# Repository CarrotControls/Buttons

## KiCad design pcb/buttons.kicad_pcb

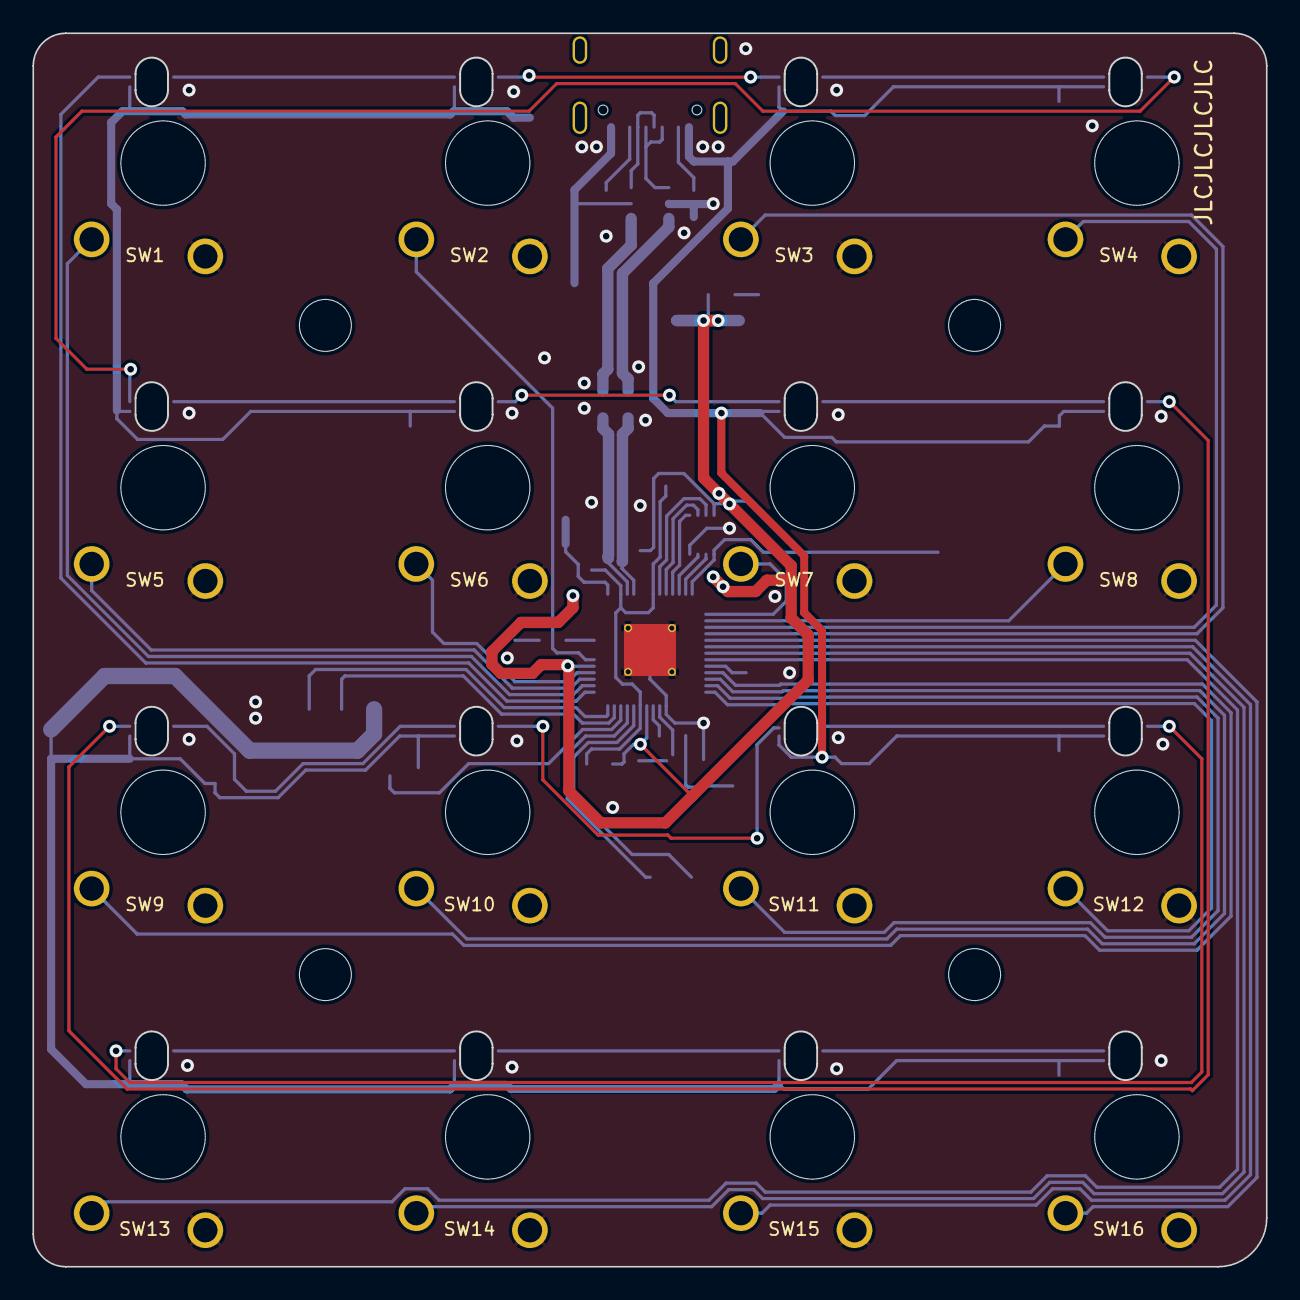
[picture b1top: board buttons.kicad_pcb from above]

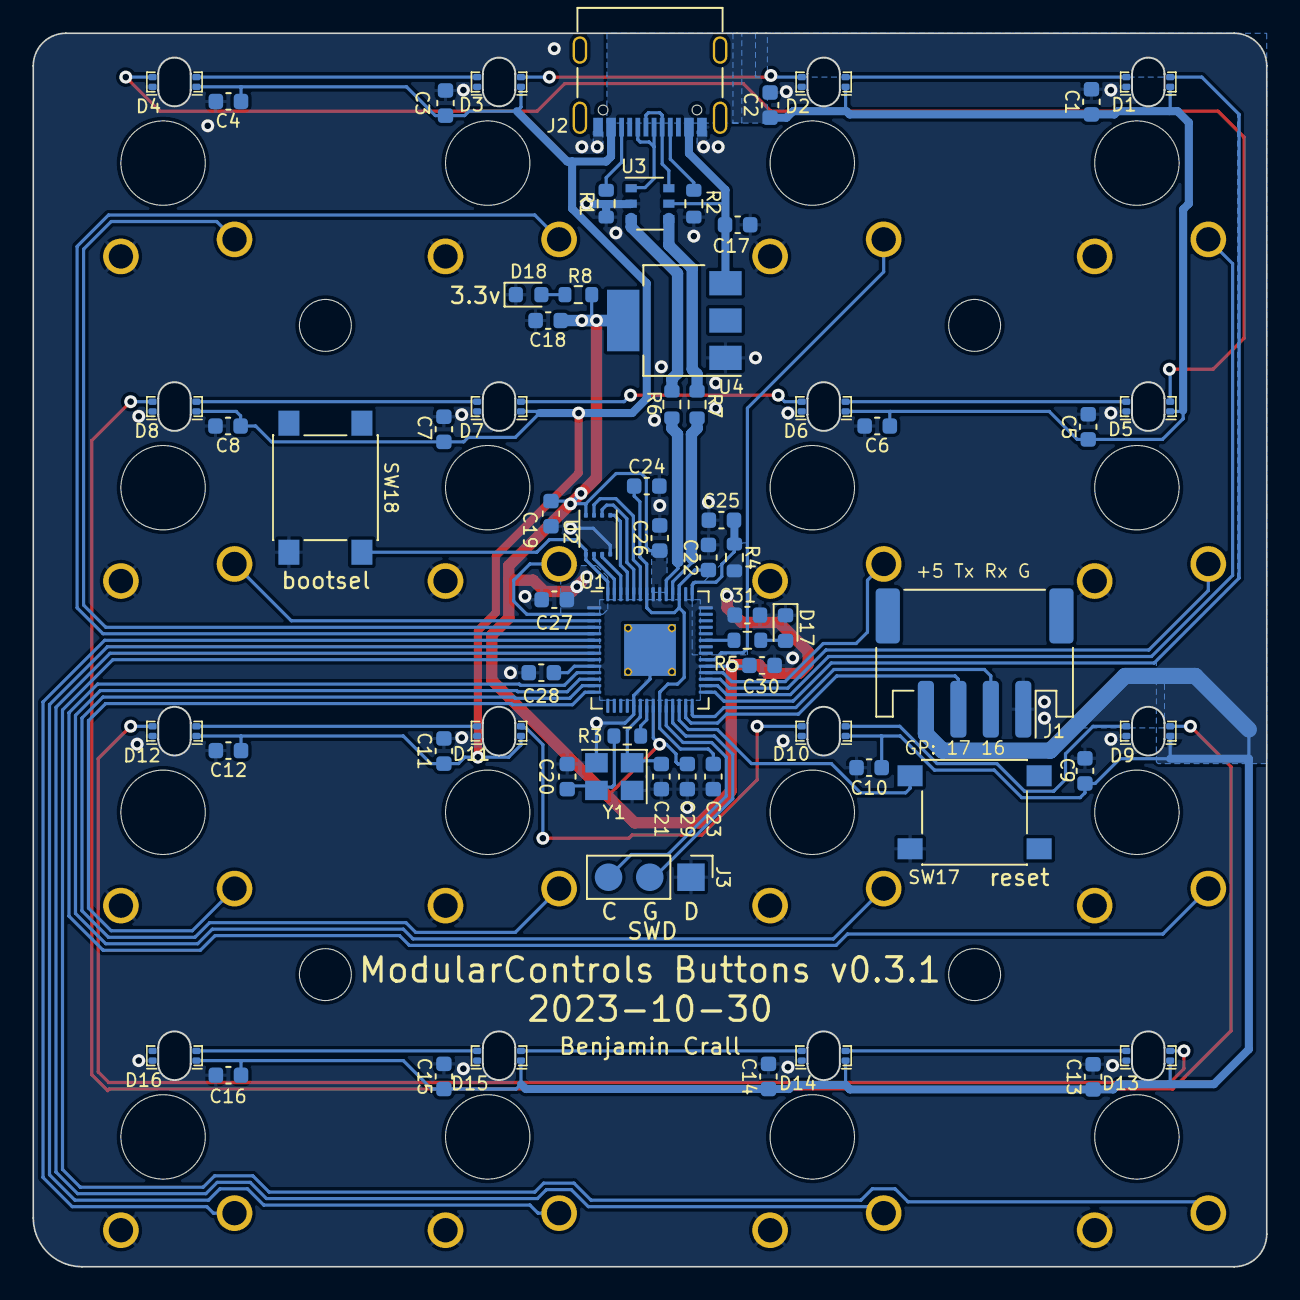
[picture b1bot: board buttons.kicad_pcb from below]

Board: 2 copper layers, 76.0 x 76.0 mm, 87 parts (67 on the bottom side), 62 nets.

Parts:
C1, C2, C3, C4, C5, C6, C7, C8, C9, C10, C11, C12, C13, C14, C15, C16, C17, C19: 10u; C_0603_1608Metric
C18: 22u; C_0603_1608Metric
C20, C21: C_XTL; C_0603_1608Metric
C22, C25: 2.2u; C_0603_1608Metric
C23, C24, C26, C27, C28, C29, C30, C31: 100n; C_0603_1608Metric
D1, D2, D3, D4, D5, D6, D7, D8, D9, D10, D11, D12, D13, D14, D15, D16: WS2812B; Neopixel - Slim Flat - Down
D17, D18: LED_GREEN; LED_0603_1608Metric
H1, H2, H3, H4: MountingHole; MountingHole_3.2mm_M3
J1: Conn_01x04; JST_PH_S4B-PH-SM4-TB_1x04-1MP_P2.00mm_Horizontal
J2: USB_C_Receptacle_USB2.0; USB_C_Receptacle_Palconn_UTC16-G
J3: Conn_01x03; PinHeader_1x03_P2.54mm_Vertical
R1, R2: 5k1; R_0603_1608Metric
R3: R; R_0603_1608Metric
R4: 1; R_0603_1608Metric
R5, R8: 470; R_0603_1608Metric
R6, R7: 22; R_0603_1608Metric
SW1, SW2, SW3, SW4, SW5, SW6, SW7, SW8, SW9, SW10, SW11, SW12, SW13, SW14, SW15, SW16: SW_SPST; SW_Gateron_MX_1.00u_Plate
SW17, SW18: SW_SPST; SW_Push_1P1T_NO_6x6mm_H9.5mm
U1: RP2040; QFN-56-1EP_7x7mm_P0.4mm_EP3.2x3.2mm_ThermalVias
U2: 8-UFDFN
U3: ip4234cz6; TSOP-6_1.65x3.05mm_P0.95mm
U4: AMS1117-3.3; SOT-223-3_TabPin2
Y1: 12MHz; Crystal_SMD_3225-4Pin_3.2x2.5mm

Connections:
+1V1: C22.1, C23.1, C24.1, U1.23 (DVDD), U1.45 (VREG_VOUT), U1.50 (DVDD)
+3V3: C18.1, C19.1, C26.1, C27.1, C28.1, C29.1, C30.1, C31.1, R4.1, R8.1, U1.1 (IOVDD), U1.10 (IOVDD), U1.22 (IOVDD), U1.33 (IOVDD), U1.42 (IOVDD), U1.44 (VREG_IN), U1.48 (USB_VDD), U1.49 (IOVDD), U2.8 (Vcc), U4.2 (VO)
+5V: C1.1, C2.1, C3.1, C4.1, C5.1, C6.1, C7.1, C8.1, C9.1, C10.1, C11.1, C12.1, C13.1, C14.1, C15.1, C16.1, C17.1, D1.4 (VDD), D2.4 (VDD), D3.4 (VDD), D4.4 (VDD), D5.4 (VDD), D6.4 (VDD), D7.4 (VDD), D8.4 (VDD), D9.4 (VDD), D10.4 (VDD), D11.4 (VDD), D12.4 (VDD), D13.4 (VDD), D14.4 (VDD), D15.4 (VDD), D16.4 (VDD), J1.4, J2.A4 (VBUS), J2.A9 (VBUS), J2.B4 (VBUS), J2.B9 (VBUS), U3.5 (Vbus), U4.3 (VI)
/microcontroller/AVDD: C25.1, R4.2, U1.43 (ADC_AVDD)
/microcontroller/QSPI_CS: SW18.1 (A), U1.56 (QSPI_SS), U2.1 (~cs)
/microcontroller/QSPI_SCLK: U1.52 (QSPI_SCLK), U2.6 (CLK)
/microcontroller/QSPI_SD0: U1.53 (QSPI_SD0), U2.5 (Dio0)
/microcontroller/QSPI_SD1: U1.55 (QSPI_SD1), U2.2 (Dio1)
/microcontroller/QSPI_SD2: U1.54 (QSPI_SD2), U2.3 (Dio2)
/microcontroller/QSPI_SD3: U1.51 (QSPI_SD3), U2.7 (Dio3)
/microcontroller/RUN: SW17.2 (B), U1.26 (RUN)
/microcontroller/SWDCLK: J3.3, U1.24 (SWCLK)
/microcontroller/SWDIO: J3.2, U1.25 (SWD)
/microcontroller/USB_CC1: J2.A5 (CC1), R2.1
/microcontroller/USB_CC2: J2.B5 (CC2), R1.1
/microcontroller/USB_DM: J2.A7 (D-), J2.B7 (D-), U3.6 (HD-)
/microcontroller/USB_DP: J2.A6 (D+), J2.B6 (D+), U3.1 (HD+)
/microcontroller/USB_PT_D+: R6.1, U3.3 (DD+)
/microcontroller/USB_PT_D-: R7.1, U3.4 (DD-)
/microcontroller/XIN: C21.1, U1.20 (XIN), Y1.1
/microcontroller/XOUT: R3.2, U1.21 (XOUT)
/microcontroller/XR: C20.1, R3.1, Y1.3
GND: C1.2, C2.2, C3.2, C4.2, C5.2, C6.2, C7.2, C8.2, C9.2, C10.2, C11.2, C12.2, C13.2, C14.2, C15.2, C16.2, C17.2, C18.2, C19.2, C20.2, C21.2, C22.2, C23.2, C24.2, C25.2, C26.2, C27.2, C28.2, C29.2, C30.2, C31.2, D1.1 (VSS), D2.1 (VSS), D3.1 (VSS), D4.1 (VSS), D5.1 (VSS), D6.1 (VSS), D7.1 (VSS), D8.1 (VSS), D9.1 (VSS), D10.1 (VSS), D11.1 (VSS), D12.1 (VSS), D13.1 (VSS), D14.1 (VSS), D15.1 (VSS), D16.1 (VSS), D17.1 (K), D18.1 (K), J1.1, J2.A1 (GND), J2.A12 (GND), J2.B1 (GND), J2.B12 (GND), J3.1, R1.2, R2.2, SW1.2 (B), SW2.2 (B), SW3.2 (B), SW4.2 (B), SW5.2 (B), SW6.2 (B), SW7.2 (B), SW8.2 (B), SW9.2 (B), SW10.2 (B), SW11.2 (B), SW12.2 (B), SW13.2 (B), SW14.2 (B), SW15.2 (B), SW16.2 (B), SW17.1 (A), SW18.2 (B), U1.19 (TESTEN), U1.57 (GND), U2.4 (GND), U3.2 (gnd), U4.1 (GND), Y1.2, Y1.4
unnamed: D1.2 (DOUT), D2.3 (DIN)
unnamed: D2.2 (DOUT), D3.3 (DIN)
unnamed: D3.2 (DOUT), D4.3 (DIN)
unnamed: D4.2 (DOUT), D5.3 (DIN)
unnamed: D5.2 (DOUT), D6.3 (DIN)
unnamed: D6.2 (DOUT), D7.3 (DIN)
unnamed: D7.2 (DOUT), D8.3 (DIN)
unnamed: D8.2 (DOUT), D9.3 (DIN)
unnamed: D9.2 (DOUT), D10.3 (DIN)
unnamed: D10.2 (DOUT), D11.3 (DIN)
unnamed: D11.2 (DOUT), D12.3 (DIN)
unnamed: D12.2 (DOUT), D13.3 (DIN)
unnamed: D13.2 (DOUT), D14.3 (DIN)
unnamed: D14.2 (DOUT), D15.3 (DIN)
unnamed: D15.2 (DOUT), D16.3 (DIN)
unnamed: D17.2 (A), R5.2
unnamed: D18.2 (A), R8.2
unnamed: R5.1, U1.37 (GPIO25)
SW1: SW1.1 (A), U1.30 (GPIO19)
SW2: SW2.1 (A), U1.34 (GPIO22)
SW3: SW3.1 (A), U1.5 (GPIO3)
SW4: SW4.1 (A), U1.4 (GPIO2)
SW5: SW5.1 (A), U1.31 (GPIO20)
SW6: SW6.1 (A), U1.32 (GPIO21)
SW7: SW7.1 (A), U1.2 (GPIO0)
SW8: SW8.1 (A), U1.3 (GPIO1)
SW9: SW9.1 (A), U1.11 (GPIO8)
SW10: SW10.1 (A), U1.12 (GPIO9)
SW11: SW11.1 (A), U1.13 (GPIO10)
SW12: SW12.1 (A), U1.14 (GPIO11)
SW13: SW13.1 (A), U1.9 (GPIO7)
SW14: SW14.1 (A), U1.8 (GPIO6)
SW15: SW15.1 (A), U1.7 (GPIO5)
SW16: SW16.1 (A), U1.6 (GPIO4)
USB_D+: R6.2, U1.47 (USB_DP)
USB_D-: R7.2, U1.46 (USB_DM)
led_data: D1.3 (DIN), U1.29 (GPIO18)
rx: J1.2, U1.28 (GPIO17)
tx: J1.3, U1.27 (GPIO16)

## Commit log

2024-01-12 move to org
2024-01-12 Added case
